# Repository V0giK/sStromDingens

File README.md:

# sStromDingens – RC-gesteuerter LED-Treiber (1W / 3W)

**[English Version](README_EN.md)**

---

## Inhaltsangabe

- [Kurzbeschreibung](#kurzbeschreibung)
- [Betriebsmodi](#betriebsmodi)
- [Schnellstart](#schnellstart)
- [Hardware](#hardware)
- [Software](#software)
- [Projektstruktur](#projektstruktur)
- [Lizenz & Mitmachen](#lizenz--mitmachen)

---

## Kurzbeschreibung

RC-gesteuerter LED-Treiber für 1W (330mA) bis 3W (830mA) LEDs – konfigurierbar über Compile-Time Defines, klein, effizient, RISC-V-basiert.

```
RC-Signal ──► CH32V003 ──► AL8862 ──► LED (1W oder 3W)
```

**Vorteile:**

- Konstantstrom ohne Vorwiderstand
- Kompakte Platine für 1W und 3W LEDs
- LED-Typ compile-time wählbar (1W = 100%, 500mA = 60%, 666mA = 80%, 830mA = 100% max Duty-Cycle)
- Fail-Safe bei Signalverlust
- 5V–12.6V Eingangsspannung (LiPo 2S–3S); möglich bis 16.8V (4S, ausserhalb AMS1117-Spezifikation)

**Ideal für:** RC-Fahrzeuge, Flugzeuge, Drohnen, Modellbau, Modellbahnen

---

## Betriebsmodi

### Dimmen / Ein-Aus

| Modus | Lötjumper DIM (PC1) | Verhalten |
|-------|---------------------|-----------|
| 🌗 **Dimmen** | GND (geschlossen) | 1ms → LED AUS, 2ms → LED AN (linear dimmen) |
| 💡 **Ein/Aus** | OFFEN | Hysterese: EIN ab 1550µs, AUS erst unter 1450µs |

### Fail-Safe

| Modus | Lötjumper ON (PD6) | Verhalten |
|-------|---------------------|-----------|
| **Fail-Safe AN** | GND (geschlossen) | LED an bei Signalverlust (>50ms) |
| **Fail-Safe AUS** | OFFEN | LED aus bei Signalverlust (>50ms) |

**Standalone-Betrieb:** Ohne RC-Empfaenger betreibbar. Lötjumper ON muss geschlossen sein – nach Timeout (50ms) geht die LED automatisch an.

---

## Schnellstart

### Was brauche ich?

| Komponente | Beschreibung | Hinweis |
|------------|--------------|---------|
| sStromDingens PCB | Hardware v2.0 | Gerber: `Hardware/KiCad/sStromDingens/production/` |
| 1W oder 3W LED | Beliebige Farbe | Konfigurierbar über Compile-Time Define (siehe Software-Abschnitt) |
| LiPo 2S-4S | 7.4V – 16.8V | 2S–3S empfohlen |
| RC-Empfänger | Beliebig | Optional bei ON-Jumper geschlossen |
| WCH-LinkE | Programmer | Für Firmware-Flash |

### In 3 Schritten zur LED-Beleuchtung

**1. Platine bestellen & bestücken**
   - Gerber-Datei: `sStromDingens_2.0.zip`
   - BOM: `bom.csv`
   - Nach Bestückungsdruck löten

**2. Firmware flashen**
   - WCH-LinkE anschließen (SWIO, GND, 3V3)
   - Firmware: `Software/firmware/firmware.hex`
   - Mit WCH-LinkUtility flashen

**3. Anschließen & Loslegen**

| Anschluss | Funktion |
|-----------|----------|
| VIN+ | LiPo Plus (5V–16.8V, max 4S) |
| VIN- | LiPo Minus (GND) |
| RC-IN | RC-Signal vom Empfänger |
| LED+ | LED Plus-Pol |
| LED- | LED Minus-Pol |

---

## Hardware

### Komponenten

| Bauteil | Beschreibung |
|---------|--------------|
| AL8862SP-13 | LED-Treiber (Konstantstrom, Step-Down) |
| CH32V003J4M6 | RISC-V Mikrocontroller (SOP-8, 24MHz) |
| AMS1117-3.3 | 3.3V Spannungsregulator |
| 15µH Induktor | Für Step-Down Wandler |
| SMF3.3CA (x2) | TVS-Diode (Überspannungsschutz) |
| SMAJ26CA | TVS-Diode (Eingangsschutz) |

### Pinbelegung CH32V003J4M6

| Pin | Funktion | Beschreibung |
|-----|----------|--------------|
| PC1 (Pin 5) | Lötjumper DIM (Mode) | Geschlossen = Linear, Offen = On/Off |
| PC2 (Pin 6) | PWM-Ausgang | → AL8862 CTRL |
| PC4 (Pin 7) | RC-Eingang | EXTI-Interrupt |
| PD6 (Pin 1) | Lötjumper ON (Fail-Safe) | Geschlossen = LED AN bei Signalverlust |

### Timer-Nutzung

| Timer | Funktion |
|-------|----------|
| TIM1 | Pulsbreitenmessung (1µs Aufloesung) |
| TIM2 | Hardware-PWM (2kHz auf PC2 via TIM2_CH2) |

### LED-Strom-Modifikation

Für höhere LED-Ströme (500mA–830mA): Einen zusätzlichen **300mΩ Widerstand** parallel zum bestehenden R4 (300mΩ) löten (huckepack). Das halbiert den Gesamtwiderstand und verdoppelt den maximalen Strom.

> ⚠️ **Wichtig:** Bei modifizierter Hardware wird der **AL8862 sehr heiss**! Zwingend eine  
> **dauerhafte zusätzliche Kühlung** erforderlich (z.B. Kühlkörper,  
> Gehäuselüfter, thermisch leitende Verbindung zur Aluminium-Platine).

| LED-Typ | Max. Strom | Duty-Cycle | Hardware |
|---------|-----------|-----------|----------|
| LED_1W (Original) | 330mA | 100% | Original |
| LED_500 | 500mA | 60% | Modifiziert |
| LED_3W / LED_666 | 666mA | 80% | Modifiziert |
| LED_830 | 830mA | 100% | Modifiziert |

> **Hinweis:** `LED_1W` laeuft auf der Original-Hardware ohne Modifikation. Alle anderen Varianten erfordern den parallel geloeteten 300mΩ Widerstand.

### Bilder

| Top | PCB | Bottom |
|-----|-----|--------|
|  |  |  |

---

## Software

### RC-Signal

| Parameter | Wert |
|-----------|------|
| Periode | 20ms (50Hz) |
| Pulsbreite | 1ms – 2ms |
| Timeout | 50ms ohne Signal |

### PWM-Ausgang

| Parameter | Wert |
|-----------|------|
| Frequenz | 2 kHz (Hardware-PWM) |
| Spannung | 0 V – 3.3 V |
| Duty-Cycle | 0 % – 100 % (1W), 0 % – 60 % (500mA), 0 % – 80 % (666mA), 0 % – 100 % (830mA) |

> **LED-Typ konfigurieren:** In `Software/firmware/User/main.c` einen der folgenden Defines aktivieren (nur eine gleichzeitig):
> ```c
> #define LED_1W   // 330mA, Original-Hardware, 100% Duty-Cycle
> // oder
> #define LED_3W   // 666mA, modifizierte Hardware, 80% Duty-Cycle
> // oder
> #define LED_500  // 500mA, modifizierte Hardware, 60% Duty-Cycle
> // oder
> #define LED_666  // 666mA, modifizierte Hardware, 80% Duty-Cycle
> // oder
> #define LED_830  // 830mA, modifizierte Hardware, 100% Duty-Cycle
> ```

### Firmware Build

**MounRiver Studio:**

```
Project → Build Project (Strg+B)
```

**CLI-Build:** Siehe [AGENTS.md](AGENTS.md) für Toolchain-Pfad, Compiler-Flags und Linker-Kommandos.

**Flashen:** WCH-LinkUtility – siehe [AGENTS.md](AGENTS.md) für Pfad.

---

## Projektstruktur

```
sStromDingens/
├── .github/          # GitHub-spezifische Konfiguration
├── Hardware/
│   ├── Documents/    # Datenblaetter (AL8862, CH32V003)
│   └── KiCad/        # KiCad-Projekt, Gerber, BOM
├── Software/
│   ├── firmware/                   # Basis-Firmware v3.0.1 (1W-3W, Hardware-PWM, LED-Auswahl)
│   │   ├── User/     # main.c (LED-Auswahl), ch32v00x_it.c, debug.c
│   │   ├── Core/     # RISC-V Core
│   │   ├── Peripheral/ # HAL-Treiber
│   │   ├── Startup/  # Startup-Code
│   │   ├── Ld/       # Linker-Skript
│   │   └── README.md # Basis-Firmware Dokumentation
│   └── firmware_700mA_afterburner/ # Afterburner v3.4.1 (3W LED, FX-Suite)
│       ├── User/     # main.c (Afterburner FX Engine)
│       ├── Core/
│       ├── Peripheral/
│       ├── Startup/
│       ├── Ld/
│       └── README.md # Afterburner Dokumentation
├── images/           # Bilder (Top, PCB, Bottom)
├── AGENTS.md         # KI-Dokumentation & Build-Referenz
├── CHANGELOG.md      # Änderungshistorie
├── LICENSE           # GNU GPLv3
├── README.md         # Deutsche Dokumentation
└── README_EN.md      # Englische Dokumentation
```

---

## Lizenz & Mitmachen

Pull Requests willkommen! Bei Fragen: [Issues](https://github.com/V0giK/sStromDingens/issues)

Lizenziert unter **[GNU GPLv3](LICENSE)**.

Änderungen: **[CHANGELOG](CHANGELOG.md)**

Entwickelt von [V0giK](https://github.com/V0giK).

---

> „Small chip, bright light – powered by RISC-V"

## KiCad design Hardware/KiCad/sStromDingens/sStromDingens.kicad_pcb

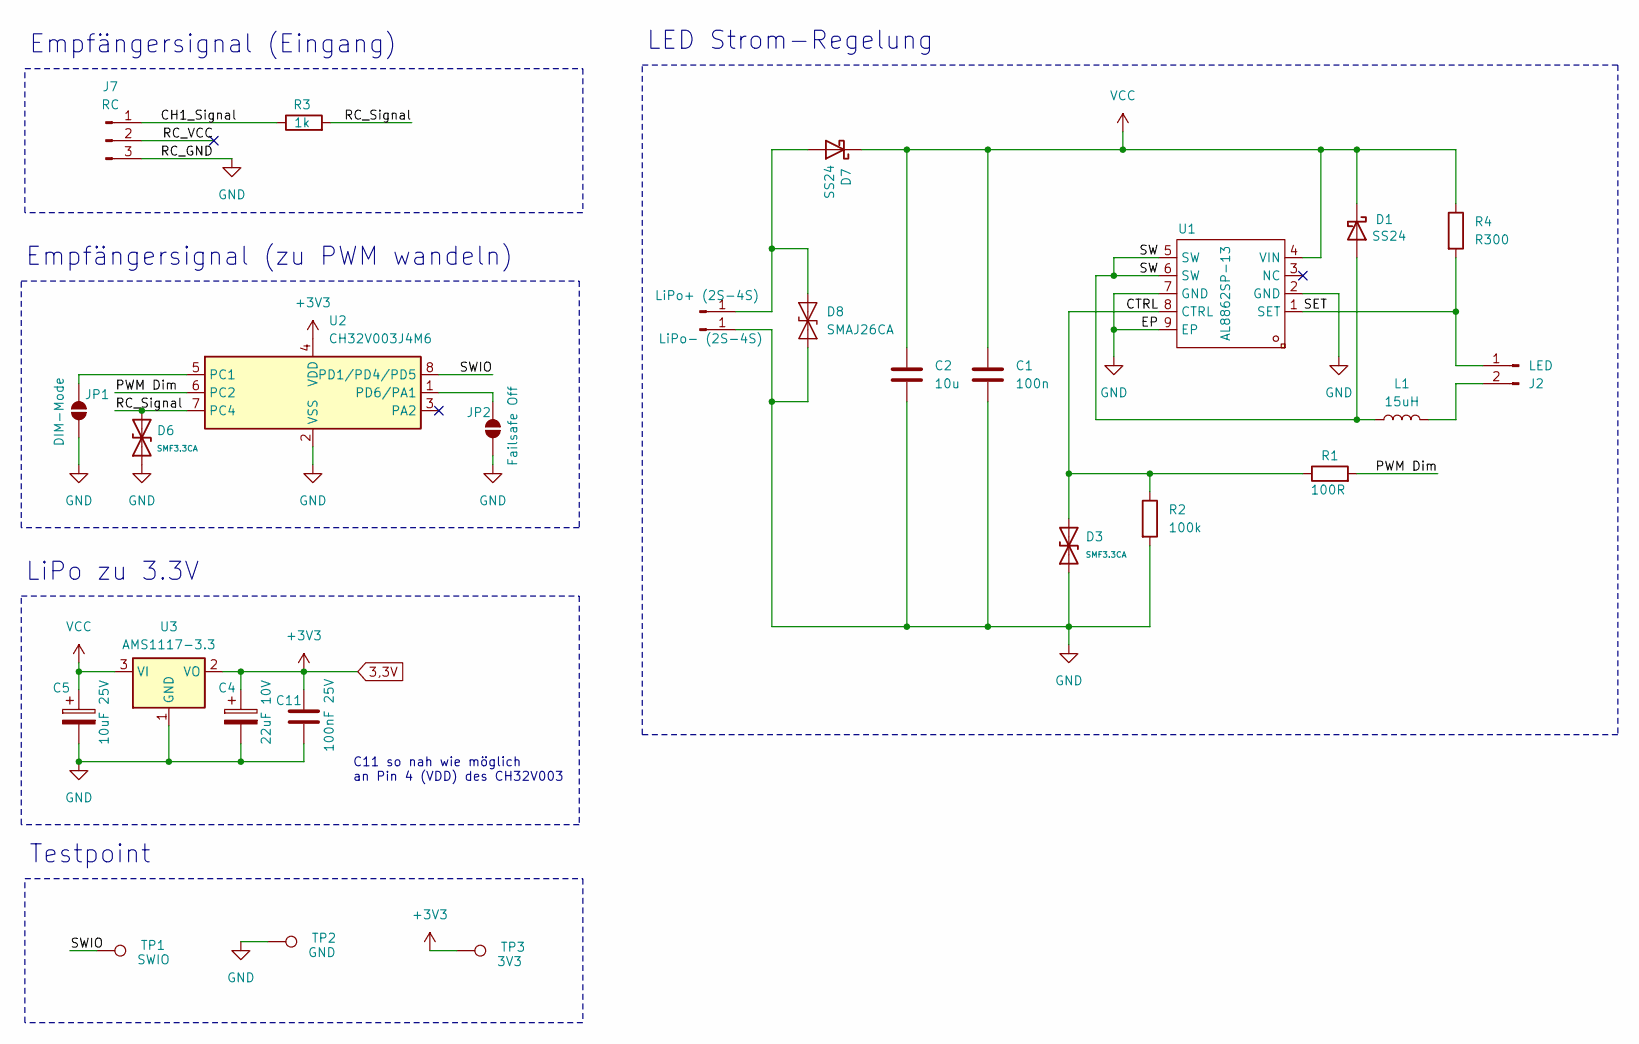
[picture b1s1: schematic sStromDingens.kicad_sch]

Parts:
C1: 100n; C_0805_2012Metric
C2: 10u; C_0805_2012Metric
C4: 22uF 10V; CASE-A_3216; MPN CA45-A-10V-22uF-K; LCSC SPN C129272
C5: 10uF 25V; CASE-B_3528; MPN CA45-B025K106T; LCSC SPN C119050
C11: 100nF 25V; C_0805_2012Metric; MPN GRM21BR71E104KA01L; LCSC SPN C86041
D1, D7: SS24; D_SMA
D3, D6: SMF3.3CA; SOD-123FL_L2.8-W1.8-LS3.7-BI; Breakdown Voltage 33.3V; Part SMF30CA; LCSC C2990493
D8: SMAJ26CA; D_SMB; MPN SMAJ26CA; LCSC SPN C148226
J1: LiPo+ (2S-4S); Conn_01x01_2.54_small
J2: LED; Conn_01x02_2.54
J3: LiPo- (2S-4S); Conn_01x01_2.54_small
J7: RC; Conn_01x03_2.54_small
JP1: DIM-Mode; SolderJumper-2_P1.3mm_Open_RoundedPad1.0x1.5mm
JP2: Failsafe Off; SolderJumper-2_P1.3mm_Open_RoundedPad1.0x1.5mm
L1: 15uH; IND-SMD_L7.1-W6.6; MPN SMMS0650-150M; LCSC SPN C149585
R1: 100R; R_0805_2012Metric
R2: 100k; R_0805_2012Metric
R3: 1k; R_0805_2012Metric
R4: R300; R_2512_6332Metric_Pad1.40x3.35mm_HandSolder
TP1: SWIO; TestPoint_Pad_D1.5mm
TP2: GND; TestPoint_Pad_D1.5mm
TP3: 3V3; TestPoint_Pad_D1.5mm
U1: AL8862SP-13; SO-8_L4.9-W3.9-P1.27-LS6.0-BL-EP; MPN AL8862SP-13; LCSC Part C526360
U2: CH32V003J4M6; JEITA_SOIC-8_3.9x4.9mm_P1.27mm; MPN CH32V003J4M6; LCSC SPN C5346354
U3: AMS1117-3.3; SOT-223-3_TabPin2; MPN AMS1117-3.3; LCSC SPN C6186

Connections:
3,3V: C4.1, C11.1, TP3.1, U2.4 (VDD), U3.2 (VO)
/CH1_Signal: J7.1, R3.1
/CTRL: D3.2 (A2), R1.1, R2.1, U1.8 (CTRL)
/PWM Dim: R1.2, U2.6 (PC2)
/RC_Signal: D6.2 (A2), R3.2, U2.7 (PC4)
/RC_VCC: J7.2
/SET: J2.1, R4.2, U1.1 (SET)
/SW: D1.2 (A), L1.1, U1.5 (SW), U1.6 (SW)
/SWIO: TP1.1, U2.8 (PD1/PD4/PD5)
GND: C1.2, C2.2, C4.2, C5.2, C11.2, D3.1 (A1), D6.1 (A1), D8.2 (A2), J3.1, J7.3, JP1.1 (A), JP2.1 (A), R2.2, TP2.1, U1.2 (GND), U1.7 (GND), U1.9 (EP), U2.2 (VSS), U3.1 (GND)
unnamed: D7.2 (A), D8.1 (A1), J1.1
unnamed: J2.2, L1.2
unnamed: JP1.2 (B), U2.5 (PC1)
unnamed: JP2.2 (B), U2.1 (PD6/PA1)
VCC: C1.1, C2.1, C5.1, D1.1 (K), D7.1 (K), R4.1, U1.4 (VIN), U3.3 (VI)

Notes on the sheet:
Empfängersignal (Eingang)
LED Strom-Regelung
C11 so nah wie möglich an Pin 4 (VDD) des CH32V003
Testpoint
LiPo zu 3.3V
Empfängersignal (zu PWM wandeln)

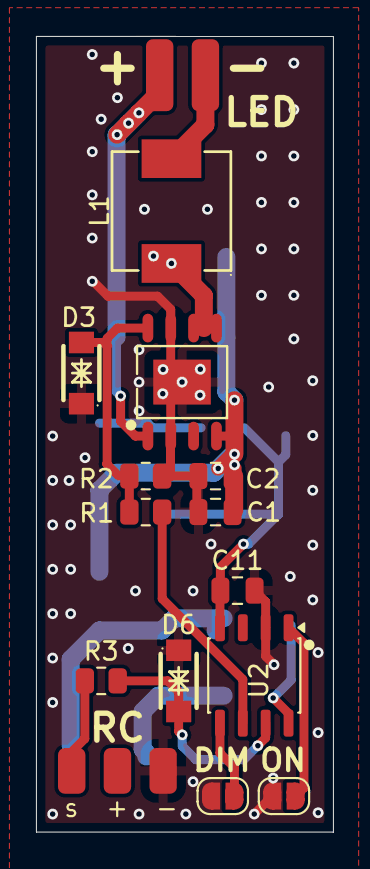
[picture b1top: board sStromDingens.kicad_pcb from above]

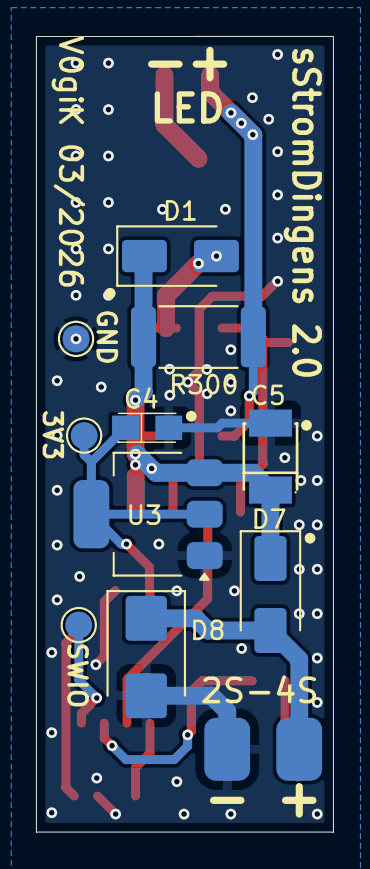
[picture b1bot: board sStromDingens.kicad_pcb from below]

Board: 2 copper layers, 16.5 x 44.2 mm, 27 parts (12 on the bottom side), 14 nets.

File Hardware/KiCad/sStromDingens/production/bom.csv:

Designator,Footprint,Quantity,Value,LCSC Part #
C1,0805,1,100n,
C11,0805,1,100nF 25V,GRM21BR71E104KA01L
C2,0805,1,10u,
C4,CASE-A_3216,1,22uF 10V,CA45-A-10V-22uF-K
C5,CASE-B_3528,1,10uF 25V,CA45-B025K106T
"D1, D7",D_SMA,2,SS24,
"D3, D6",SOD-123FL_L2.8-W1.8-LS3.7-BI,2,SMF3.3CA,C2990493
D8,D_SMB,1,SMAJ26CA,C148226
J1,Conn_01x01_2.54_small,1,LiPo+ (2S-4S),
J2,Conn_01x02_2.54,1,LED,
J3,Conn_01x01_2.54_small,1,LiPo- (2S-4S),
J7,Conn_01x03_2.54_small,1,RC,
L1,IND-SMD_L7.1-W6.6,1,15uH,SMMS0650-150M
R1,0805,1,100R,
R2,0805,1,100k,
R3,0805,1,1k,
R4,2512,1,R300,
TP1,TestPoint_Pad_D1.5mm,1,SWIO,
TP2,TestPoint_Pad_D1.5mm,1,GND,
TP3,TestPoint_Pad_D1.5mm,1,3V3,
U1,SO-8_L4.9-W3.9-P1.27-LS6.0-BL-EP,1,AL8862SP-13,C526360
U2,JEITA_SOIC-8_3.9x4.9mm_P1.27mm,1,CH32V003J4M6,C5346354
U3,SOT-223-3_TabPin2,1,AMS1117-3.3,AMS1117-3.3

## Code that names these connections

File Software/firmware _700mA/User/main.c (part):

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 * @brief Initialisiert alle GPIO-Pins
 * 
 * Konfiguration:
 * - PC4: RC-Eingang (IN_FLOATING, da externer 3.3V-Pegel)
 * - PC2: PWM-Ausgang (Push-Pull fuer AL8862 CTRL)
 * - PC1: Mode-Jumper (Pull-Up, GND = Linear-Modus)
 * - PD6: Fail-Safe-Jumper (Pull-Up, GND = LED AN bei Signalverlust)
 */
void GPIO_Init_Custom(void)
{
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    GPIO_InitStructure.GPIO_Mode = GPIO_Mode_IN_FLOATING;
    GPIO_Init(RC_INPUT_PORT, &GPIO_InitStructure);

    /* PWM-Ausgang: Push-Pull fuer AL8862 CTRL-Pin */
    GPIO_InitStructure.GPIO_Pin = PWM_OUTPUT_PIN;
    GPIO_InitStructure.GPIO_Mode = GPIO_Mode_Out_PP;
    GPIO_Init(PWM_OUTPUT_PORT, &GPIO_InitStructure);
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/**
 * @brief Konfiguriert EXTI fuer RC-Signal-Erkennung
 * 
 * EXTI-Line4 wird auf PC4 geroutet. Bei jeder Flanke (Rising und Falling)
 * wird der EXTI7_0_IRQHandler aufgerufen.
 * 
 * Interrupt-Prioritaet: 0 (hoechste, damit RC-Signal nicht verpasst wird)
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    EXTI_InitTypeDef EXTI_InitStructure;
    NVIC_InitTypeDef NVIC_InitStructure;

    /* PC4 mit EXTI-Line4 verbinden */
    GPIO_EXTILineConfig(GPIO_PortSourceGPIOC, GPIO_PinSource4);

    /* EXTI-Line4 konfigurieren: Rising + Falling Edge */
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        {
            /*------------------------------------------------------------*/
            /* FAIL-SAFE: Bei Signalverlust LED auf definierten Zustand  */
            /* failsafe_high = 1 (PD6=GND) -> pwm_duty = PWM_MAX_DUTY -> LED AN (max) */
            /* failsafe_high = 0 (PD6=OFFEN) -> pwm_duty = 0 -> LED AUS   */
            /*------------------------------------------------------------*/
            pwm_duty = failsafe_high ? PWM_MAX_DUTY : 0;
        }
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
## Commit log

2026-02-22 Initial commit: v1.0.0 - RC to PWM converter for 1W LED
2026-02-22 Remove planned future development section
2026-02-22 Remove Coding-Standards section
2026-02-23 Add debug files and clangd config, remove printf to fit in 16KB flash
2026-02-23 Update AGENTS.md with CH32V003 datasheet references
2026-02-23 Add hardware datasheets (CH32V003, AL8862)
2026-02-23 Add CH32V003 and AL8862 PDF datasheets, enable PDF tracking in gitignore
2026-02-23 Update firmware version to 1.0.1, add PWM frequency to README
2026-02-23 Bump version to 1.0.1, fix PWM frequency to 1000Hz
2026-02-23 Clarify CHANGELOG - hardware unchanged in v1.0.1
2026-02-23 Add versioning schema to AGENTS.md and CHANGELOG.md
2026-03-10 Implement Software-PWM, update to v1.1.0
    - Replace Hardware-PWM (TIM1) with Software-PWM (TIM2) for reliable output
    - Add TIM2 IRQ handler for PWM generation (~100Hz)
    - Fix race condition: copy rc_pulse_us before clearing rc_valid
    - Update author to V0giK, copyright to 2026
    - Update AGENTS.md: timer usage, build process, version
    - Update README.md: Software-PWM, pinout, RC timeout
2026-03-10 Add v1.1.0 to CHANGELOG
2026-03-17 Implement v1.2.0: EXTI-based RC measurement, TIM2 PWM, 24MHz system clock
    - RC-Signal measurement via EXTI interrupt (rising + falling edge)
    - TIM2 software PWM at 100Hz (100 steps resolution)
    - Linear mode: 1ms→LED OFF, 2ms→LED ON (proportional dimming)
    - On/Off mode: <1.5ms→LED OFF, ≥1.5ms→LED ON
    - Fail-Safe: PD4=GND → LED ON on signal loss
    - Fix: Timer config for 24MHz system clock (TIM1 prescaler, TIM2 period)
2026-03-17 Add GitHub prompts and interactive BOM
    - Add firmware-code-review.prompt.md for AI-assisted code review
    - Add interactive BOM (ibom.html) for hardware assembly reference
2026-03-17 Update KiCad production files
2026-03-17 Refactor: Replace magic numbers with named constants
    - Add RC_PULSE_MIN_VALID (800µs) and RC_PULSE_MAX_VALID (2500µs) defines
    - Add PWM_STEPS (100) define for PWM resolution
    - Fix include style: use "ch32v00x_it.h" instead of <ch32v00x_it.h>
    - Update comments to reference new defines
    - Improves code maintainability and readability
2026-03-17 Fix: Update firmware-code-review prompt to 24MHz
    - Correct processor frequency from 48MHz to 24MHz to match actual hardware configuration
2026-03-17 Fix: Replace German umlauts and special chars with ASCII equivalents
    - Replace umlauts (ae, oe, ue) for better encoding compatibility
    - Replace micro symbol (us) with ASCII 'us'
    - Replace arrow symbol (->) with ASCII '->'
    - Prevents encoding issues on different systems/editors
2026-03-17 Redesign README.md in kerosin style, change license to GPLv3
    - Add emojis to section headers for better readability
    - Restructure README with clear sections (Features, Components, Hardware, Software)
    - Change license from MIT to GPLv3 (ensures OpenSource stays OpenSource)
    - Add GPLv3 license headers to main.c and ch32v00x_it.c
    - Add author section with GitHub link
    - Add project slogan: 'Small chip, bright light – powered by RISC-V'
2026-03-25 Hardware v2.0: Add TVS protection, move Failsafe to Pin 1
    - Add SMF3.3CA TVS diodes for input protection (LiPo)
    - Add SMAJ26CA TVS diode for LED output protection
    - Remove SMAJ15A overvoltage protection
    - Move Failsafe jumper from Pin 8 (PD4) to Pin 1 (PD6)
2026-03-25 Firmware v2.0.0: Update Failsafe pin for Hardware v2.0
    - Change Failsafe pin from PD4 to PD6 (Pin 1)
    - Bump version to 2.0.0
    - Compatible only with Hardware v2.0
2026-03-25 Docs: Update documentation for v2.2.0
    - Update pin assignments in AGENTS.md and README.md
    - Add CHANGELOG entry for v2.2.0
    - Update component lists with new TVS diodes
    - Change license to GPLv3
2026-03-25 Revise input voltage range for LED driver
    Updated input voltage specification for the LED driver.
2026-03-25 Docs: Korrigiere Eingangsspannungsangabe (LiPo 2S-3S)
2026-03-25 Docs/Firmware: Korrigiere Fail-Safe Pin von PD4 auf PD6 (Hardware v2.0)
2026-03-25 Add *.lck to .gitignore for KiCad lock files
2026-03-25 Docs: Translate firmware-code-review.prompt.md to English
2026-03-25 Docs: Update firmware status to 'fertig' in AGENTS.md
2026-03-27 Docs: Add hardware images section to README.md
2026-03-27 Docs: Update project title to emphasize LED lighting purpose
2026-03-27 Docs: Complete restructure of README.md for better usability
2026-03-27 Docs: Add English README_EN.md with language switcher
2026-03-27 Resize images to 600px height, backup originals in images/original/
2026-03-27 Docs: Update voltage specs - 2S-3S recommended, 6S possible outside AMS1117 spec
2026-03-27 Docs: Update AGENTS.md - fix Fail-Safe pin (PD4→PD6), update project structure
2026-03-27 Docs: Update CH32V003J4M6 pinout documentation
2026-03-27 Docs: Update jumper labels to match PCB silkscreen (DIM, ON)
2026-04-12 Docs: Reorganize README structure, update title and project description
2026-04-12 Docs: Add standalone operation note, mark RC receiver as optional
2026-04-12 Cleanup: Remove IDE files and original images from repo
    - Remove .clangd, .template, firmware.wvproj from git tracking
    - Add .clangd, .template, *.wvproj to .gitignore
    - Remove images/original/ (duplicates of images/)
2026-04-12 Hardware: Set STEP export path in KiCad project
2026-04-18 Docs/Hardware: LiPo-Spec von 6S auf 4S korrigiert (AMS1117 max. 15V)
2026-04-18 Fix: Verbleibende 6S/26V-Referenzen auf 4S/16.8V korrigiert
2026-04-18 Fix: ibom.html mit korrigierten 4S-Daten aktualisiert
2026-04-28 Cleanup: KiCad .history/ zu .gitignore hinzugefügt
2026-04-28 Hardware: KiCad-Projektdateien auf neue Version aktualisiert
2026-04-28 Software: 700mA Firmware-Variante hinzugefügt
2026-05-01 Bump to v3.4.0: Hardware-PWM, Afterburner FX, docs cleanup
    Firmware:
    - Basis-Firmware v3.0.0: Software-PWM -> TIM2 Hardware-PWM @ 2kHz
    - Basis-Firmware: compile-time LED-Auswahl (LED_1W / LED_3W)
    - Basis-Firmware: Hysterese im On/Off-Modus (1450/1550us)
    - Afterburner v3.4.0: Neue State-Machine mit FX-Suite
    (Spool-Up, Ramp-Down, Cool-Down, Burst, Flame-Out, Flicker, Heat-Shimmer)
2026-05-03 Bump to v3.0.1/v3.4.1: Expand LED variants (330-830mA), PWM_MAX_DUTY config, version sync
2026-05-03 Set default LED to LED_1W (Original-Hardware, 330mA)
2026-05-03 docs: Fix ASCII umlaut replacements in German markdown files

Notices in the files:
Software/firmware _700mA/User/main.c:
Copyright (C) 2026 V0giK
sStromDingens is free software: you can redistribute it and/or modify
it under the terms of the GNU General Public License as published by
the Free Software Foundation, either version 3 of the License, or
(at your option) any later version.
README.md:
License: GPLv3
